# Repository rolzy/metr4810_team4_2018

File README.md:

# metr4810_team4_2018
Repository for Team 4 for METR4810 Sem1 2018

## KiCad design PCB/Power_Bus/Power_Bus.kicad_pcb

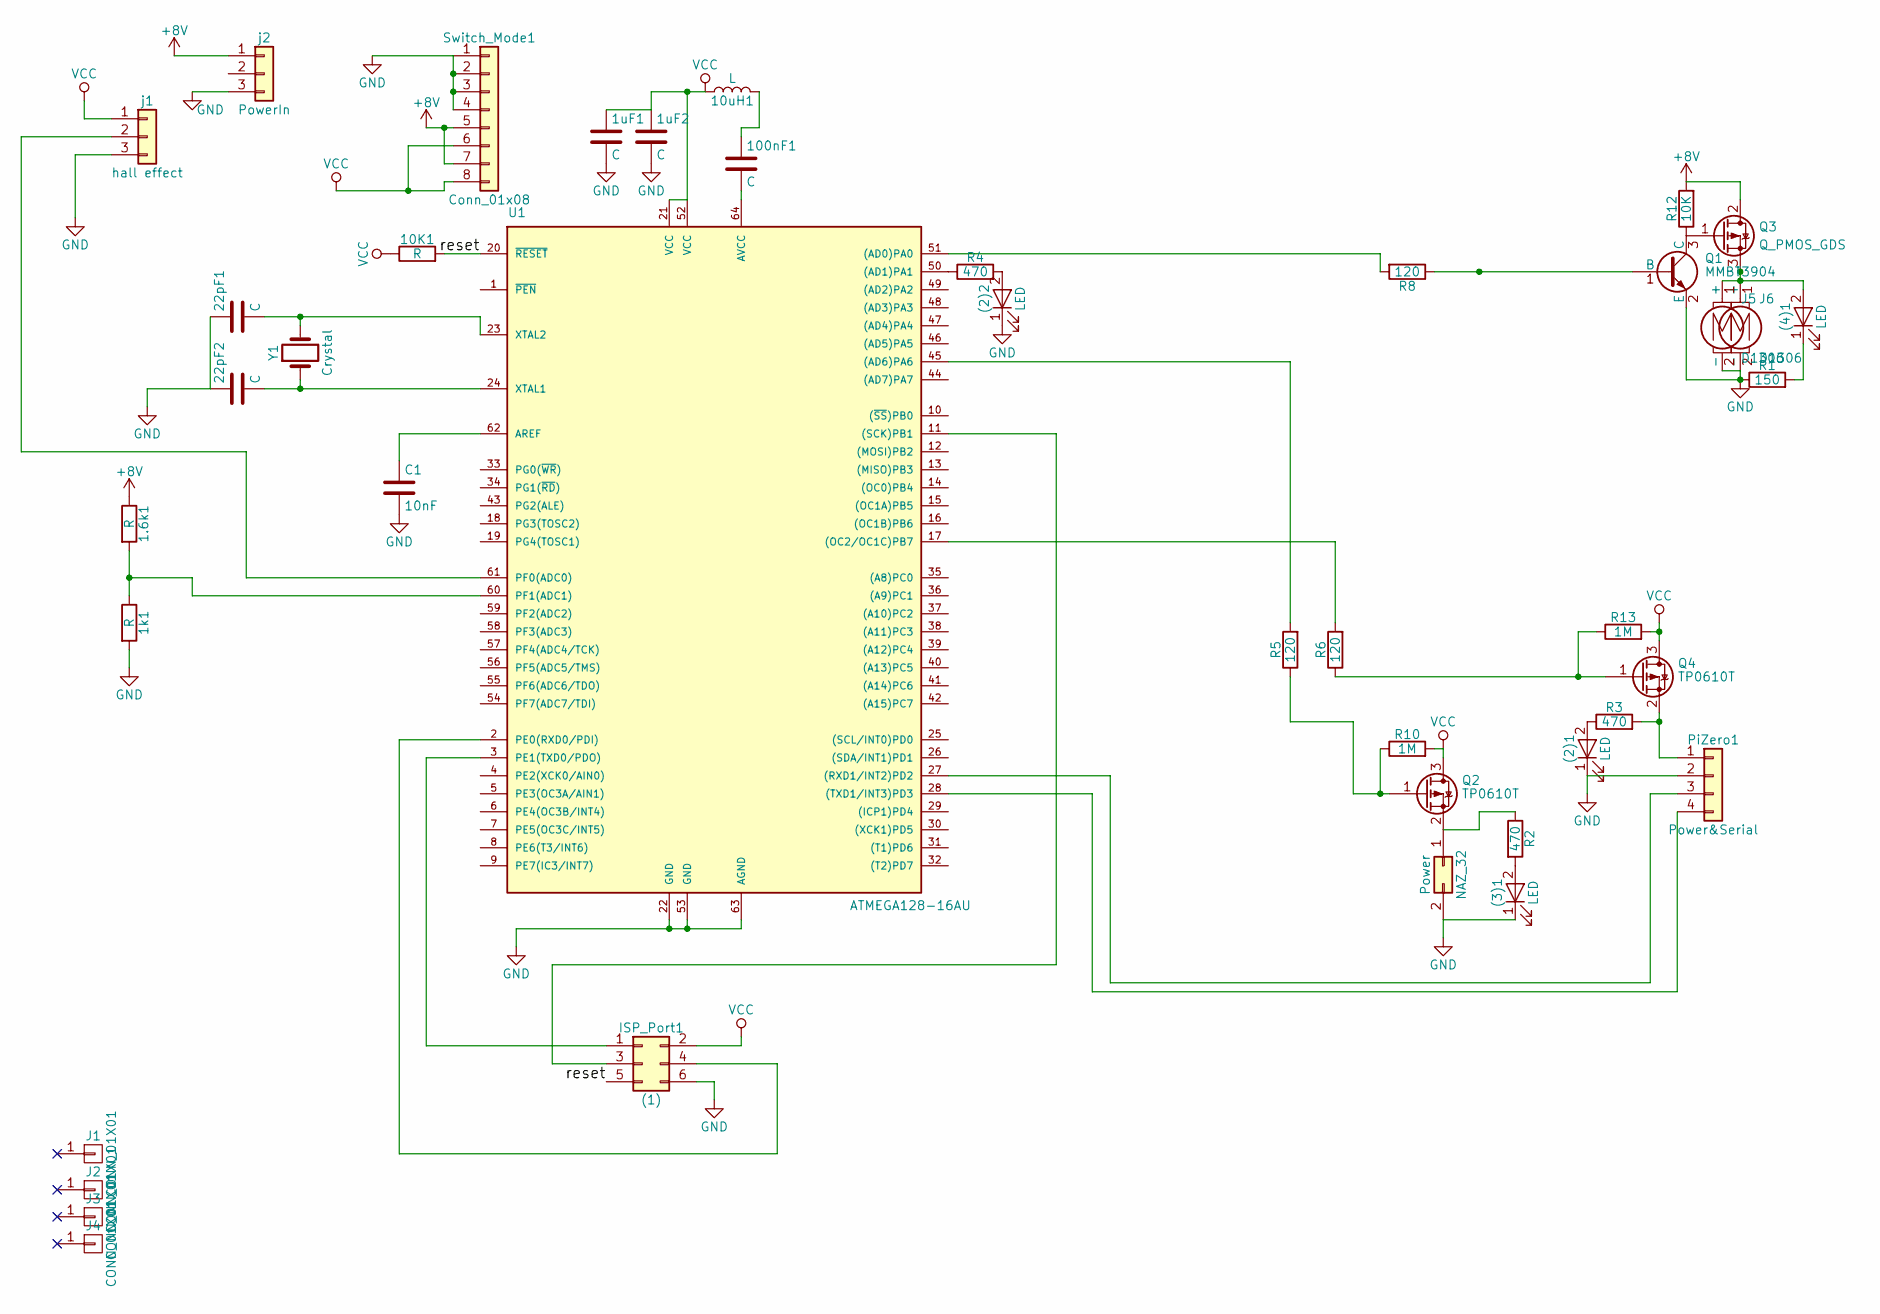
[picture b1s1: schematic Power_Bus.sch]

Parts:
1.6k1, 1k1, 10K1: R; R_0805_HandSoldering
1uF1, 1uF2, 22pF1, 22pF2, 100nF1: C; C_0805_HandSoldering
10uH1: L; L_0805_HandSoldering
(2)1, (2)2, (3)1, (4)1: LED; LED_0603_HandSoldering
C1: 10nF; C_0805_HandSoldering
ISP_Port1: (1); Pin_Header_Straight_2x03_Pitch2.54mm
J1, J2, J3, J4: CONN_01X01; MountingHole_3.2mm_M3
J5, J6: D1306; JST_EH_S02B-EH_02x2.50mm_Angled
NAZ_32: Power; JST_EH_S02B-EH_02x2.50mm_Angled
PiZero1: Power&Serial; Pin_Header_Straight_1x04_Pitch2.54mm
Q1: MMBT3904; SOT-23
Q2, Q4: TP0610T; SOT-323_SC-70
Q3: Q_PMOS_GDS; TO-252-3_TabPin2
R1: 150; R_0805_HandSoldering
R2, R3, R4: 470; R_0805_HandSoldering
R5, R6, R8: 120; R_0805_HandSoldering
R10, R13: 1M; R_0805_HandSoldering
R12: 10K; R_0805_HandSoldering
Switch_Mode1: Conn_01x08; Pin_Header_Straight_Switch_Mode
U1: ATMEGA128-16AU; QFP80P1600X1600X120-64N
Y1: Crystal; Crystal_HC49-4H_Vertical
j1: hall effect; Pin_Header_Straight_1x03_Pitch2.54mm
j2: PowerIn; JST_EH_S03B-EH_03x2.50mm_Angled

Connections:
+8V: 1.6k1.1, Q3.2 (D), R12.2, Switch_Mode1.5, Switch_Mode1.7, j2.1
/reset: 10K1.2, ISP_Port1.5, U1.20 (~RESET)
GND: 1k1.2, 1uF1.2, 1uF2.2, 22pF1.1, 22pF2.1, (2)1.1 (K), (2)2.1 (K), (3)1.1 (K), C1.2, ISP_Port1.6, J5.2 (-), J6.2 (-), NAZ_32.2, PiZero1.2, Q1.2 (E), R1.1, Switch_Mode1.1, Switch_Mode1.2, Switch_Mode1.3, Switch_Mode1.4, U1.22 (GND), U1.53 (GND), U1.63 (AGND), j1.3, j2.3
unnamed: 1.6k1.2, 1k1.1, U1.60 (PF1(ADC1))
unnamed: 22pF1.2, U1.23 (XTAL2), Y1.2
unnamed: 22pF2.2, U1.24 (XTAL1), Y1.1
unnamed: 10uH1.2, 100nF1.1
unnamed: 100nF1.2, U1.64 (AVCC)
unnamed: (2)1.2 (A), R3.1
unnamed: (2)2.2 (A), R4.2
unnamed: (3)1.2 (A), R2.2
unnamed: (4)1.1 (K), R1.2
unnamed: (4)1.2 (A), J5.1 (+), J6.1 (+), Q3.3 (S)
unnamed: C1.1, U1.62 (AREF)
unnamed: ISP_Port1.1, U1.3 (PE1(TXD0/PDO))
unnamed: ISP_Port1.3, U1.11 ((SCK)PB1)
unnamed: ISP_Port1.4, U1.2 (PE0(RXD0/PDI))
unnamed: NAZ_32.1, Q2.2 (S), R2.1
unnamed: PiZero1.1, Q4.2 (S), R3.2
unnamed: PiZero1.3, U1.27 ((RXD1/INT2)PD2)
unnamed: PiZero1.4, U1.28 ((TXD1/INT3)PD3)
unnamed: Q1.1 (B), R8.1
unnamed: Q1.3 (C), Q3.1 (G), R12.1
unnamed: Q2.1 (G), R5.1, R10.1
unnamed: Q4.1 (G), R6.1, R13.1
unnamed: R4.1, U1.50 ((AD1)PA1)
unnamed: R5.2, U1.45 ((AD6)PA6)
unnamed: R6.2, U1.17 ((OC2/OC1C)PB7)
unnamed: R8.2, U1.51 ((AD0)PA0)
unnamed: U1.61 (PF0(ADC0)), j1.2
VCC: 1uF1.1, 1uF2.1, 10K1.1, 10uH1.1, ISP_Port1.2, Q2.3 (D), Q4.3 (D), R10.2, R13.2, Switch_Mode1.6, Switch_Mode1.8, U1.21 (VCC), U1.52 (VCC), j1.1

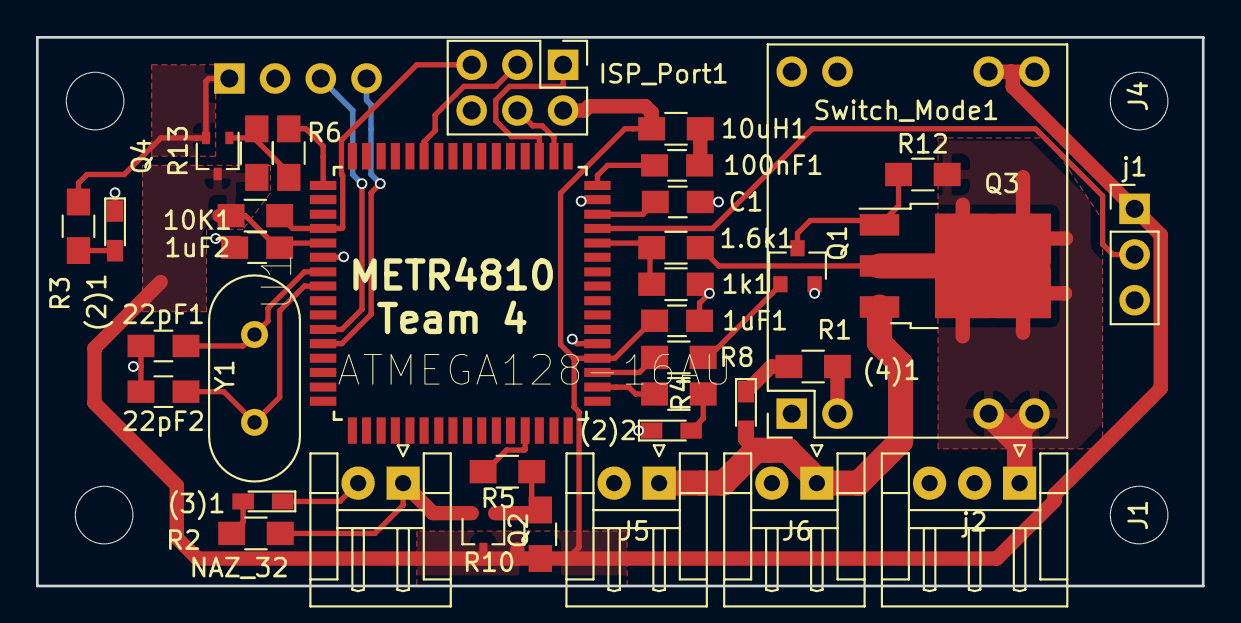
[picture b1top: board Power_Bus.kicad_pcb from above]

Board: 2 copper layers, 64.8 x 30.5 mm, 42 parts (1 on the bottom side), 31 nets.

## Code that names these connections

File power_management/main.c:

/*
 * GccApplication2.c
 *
 * Created: 21/05/2018 12:12:40 PM
 * Author : lachl
 */ 

#include <avr/io.h>


#include <avr/io.h>
//#ifndef F_CPU
//#define F_CPU 16000000UL // 16 MHz clock speed

#include <util/delay.h>

void Init_Power (void){
	DDRA |= (1 << PA0) || DDRA |= (1 << PA1) || DDRA |= (1 << PA6) || DDRB |= (1 << PB7);
	PORTB |= (0 << PB7) || PORTA |= (0 << PA0) || PORTA |= (0 << PA1) || PORTA |= (0 << PA6);	
}

void Cycle_Telemetry (void){
	PORTB |= (1 << PB7);
	_delay_ms(3000);
	PORTB |= (0 << PB7);	
}

void Cycle_Orientation (void){
	PORTA |= (1 << PA0) || PORTA |= (1 << PA6);
	_delay_ms(3000);
	PORTA |= (0 << PA0) || PORTA |= (0 << PA6);
}

int main(void)
{
	
	
	/* Replace with your application code */
	while (1)
 	{
// 		PORTC |= (1<<PC0);
		
		
//  		PORTC = 0xFF; //Turns ON All LEDs
//  		_delay_ms(2000); //1 second delay
//  		PORTC= 0x00; //Turns OFF All LEDs
//  		_delay_ms(2000); //1 second delay
	}
}

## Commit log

2018-03-07 Betaflight src file
2018-03-11 PymultiWii
2018-03-12 c# mqtt client added
2018-03-12 config file pasing
2018-03-12 mqtt aggregator arduino blink working
2018-03-13 add auto start to aggregator
2018-03-13 fixed packages in VS
2018-03-13 add RGB led for testing
2018-03-13 aggregator dev- implementing malloc currently broken
2018-03-13 code refactoring
2018-03-13 add disconect to base stations app \n add error checking for serial messages
2018-03-13 add image transfer via mqtt
2018-03-13 add zoom feature
2018-03-13 tidied code
2018-03-14 add web service control
2018-03-15 Serial connection attempt with clean&base flight
2018-03-17 Hackflight attempt
2018-03-18 msp peripherals
2018-03-21 Replace msp repo with own folder
2018-03-22 Control speed from serial
2018-03-26 Initial PID attempt
2018-03-27 config's now connect to MQTT server on local host
2018-03-27 add file saving and prelim data graphing
2018-03-27 add tree to view files and control of orentation
2018-03-28 Finish PID first attempt
2018-04-02 PID code in c++
2018-04-03 PID inloop testing
2018-04-09 Variable storage MSP function:
2018-04-09 Add my own betaflight files
2018-04-11 PID almost finished
2018-04-14 PID fixes
2018-04-18 PID attempt #74389210
2018-04-22 PID ready for operation
2018-04-22 Added interface for dsn, still need to incorperate mqtt
2018-04-22 implemented dsn using serial
2018-04-23 implements Deep Space Network
2018-04-23 Removed binary files
2018-04-25 Start sensor fusion
2018-04-25 DSN use is now optitional
2018-04-25 Add CAD files
2018-04-26 camera config settings - not tested
2018-04-27 MQTT & libconfig integrated to orientation control
2018-04-29 added error handeling for mqtt disconection
2018-04-29 image auto sizes on load
2018-04-30 MQTT to MSP aggregator finished
2018-04-30 re did lachlans pcb layout
2018-04-30 removed gerbers from source
2018-05-06 added team name to silkscreen
2018-05-07 This commit adds super resolution test code
2018-05-10 Add PID tuning feature:
2018-05-16 Attitude determination with magnetometer
2018-05-20 rotate mosfets in sch. not in the pcb
2018-05-21 added gamma control for Images using Emgu CV
2018-05-22 Origin search sequence & optimisation
2018-05-22 Add power management code
2018-05-24 Add calibration and start MSP functions, and improving on search sequence
2018-05-24 Start UI for orientation
2018-05-24 moved agg code, added error checking for live feed
2018-05-24 added key's for power cycle
2018-05-24 updated last will
2018-05-24 Added Orientation Controls and Camera Config to Base Station GUI
2018-05-24 Added commands for camera configuration
2018-05-26 updated powere ystem intefaceing
2018-05-26 Motor debugging
2018-05-26 Minor changes to camera config defaults
2018-05-27 added model
2018-05-27 minor gui fixes (anchor gamma slider, increase dekat for web service)
2018-05-27 Gyro fusion:
2018-05-27 fixed mesage payload issue with aggregrator
2018-05-27 Set defaults for camera config
2018-05-27 Comments
2018-05-27 added error checking and comments
2018-05-27 merge
2018-05-27 Comments Completed
